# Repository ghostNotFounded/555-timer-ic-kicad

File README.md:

# 555 Timer IC Project using KiCad

## Overview
This repository contains the schematic and PCB design files for a 555 Timer IC circuit created using KiCad. The project was undertaken as part of the learning process for KiCad and to contribute to joining the robotics team at CRiSS Robotics on campus.

## Contents
- **Schematic**: Contains the schematic design of the 555 Timer IC circuit.
- **PCB Layout**: Includes the PCB layout design based on the schematic.

## Purpose
The purpose of this project was to:
- Learn KiCad, a popular open-source EDA tool for circuit design and PCB layout.
- Gain hands-on experience in designing a simple circuit using a widely-used IC, the 555 Timer.
- Prepare to contribute to the robotics team at CRiSS Robotics, showcasing skills in circuit design and layout.

## How to Use
1. Clone or download the repository to your local machine.
2. Open the schematic and PCB layout files using KiCad.
3. Review the designs, make any necessary modifications, and generate Gerber files for manufacturing if required.

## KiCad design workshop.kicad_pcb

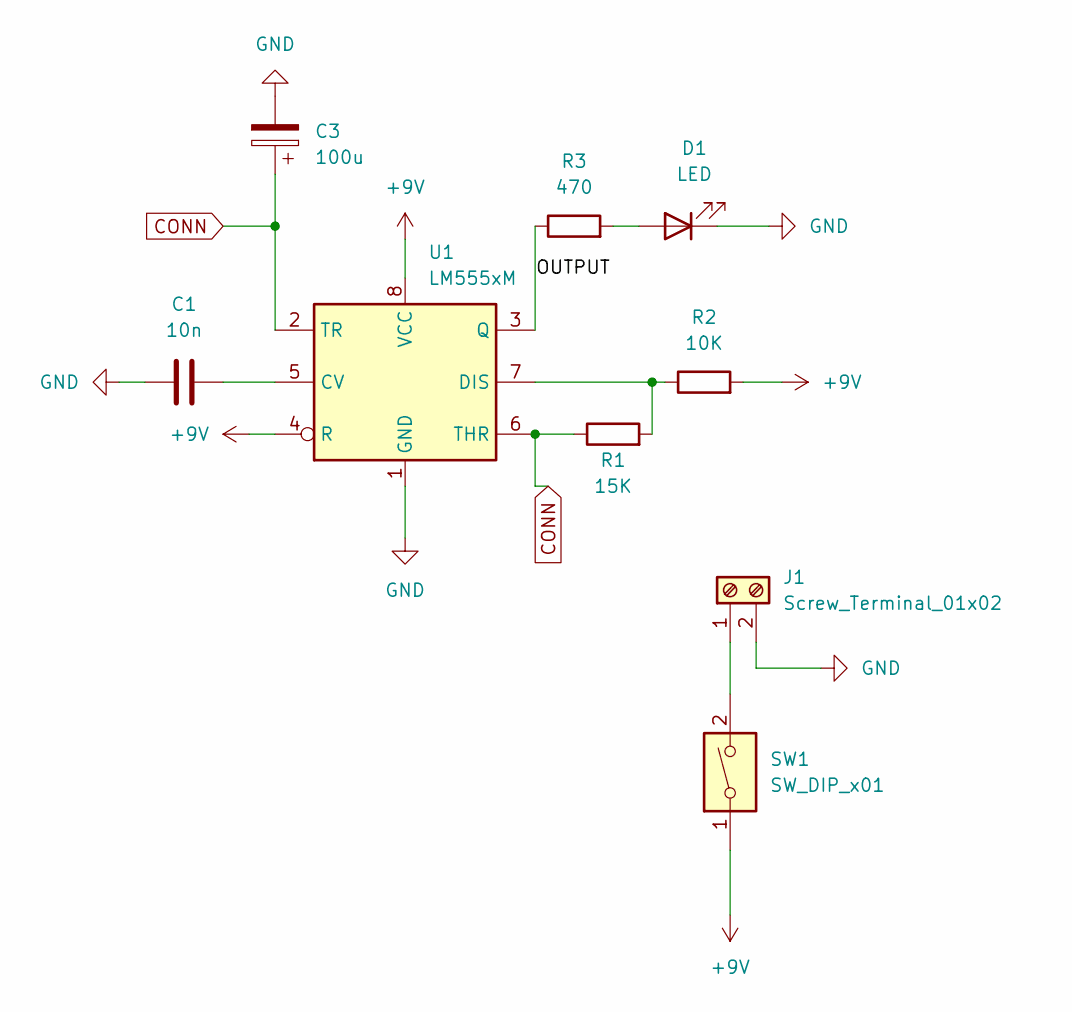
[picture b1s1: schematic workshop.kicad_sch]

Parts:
C1: 10n; C_Disc_D4.7mm_W2.5mm_P5.00mm
C3: 100u; CP_Radial_D12.5mm_P7.50mm
D1: LED; LED_D5.0mm
J1: Screw_Terminal_01x02; BarrelJack_CUI_PJ-063AH_Horizontal
R1: 15K; R_Axial_DIN0207_L6.3mm_D2.5mm_P10.16mm_Horizontal
R2: 10K; R_Axial_DIN0207_L6.3mm_D2.5mm_P10.16mm_Horizontal
R3: 470; R_Axial_DIN0207_L6.3mm_D2.5mm_P10.16mm_Horizontal
SW1: SW_DIP_x01; SW_DIP_SPSTx01_Slide_6.7x4.1mm_W7.62mm_P2.54mm_LowProfile
U1: LM555xM; SOIC-8_3.9x4.9mm_P1.27mm

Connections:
+9V: R2.2, SW1.1, U1.4 (R), U1.8 (VCC)
/OUTPUT: R3.1, U1.3 (Q)
CONN: C3.1, R1.1, U1.2 (TR), U1.6 (THR)
GND: C1.1, C3.2, D1.1 (K), J1.2, U1.1 (GND)
unnamed: D1.2 (A), R3.2
unnamed: J1.1, SW1.2
unnamed: C1.2, U1.5 (CV)
unnamed: R1.2, R2.1, U1.7 (DIS)

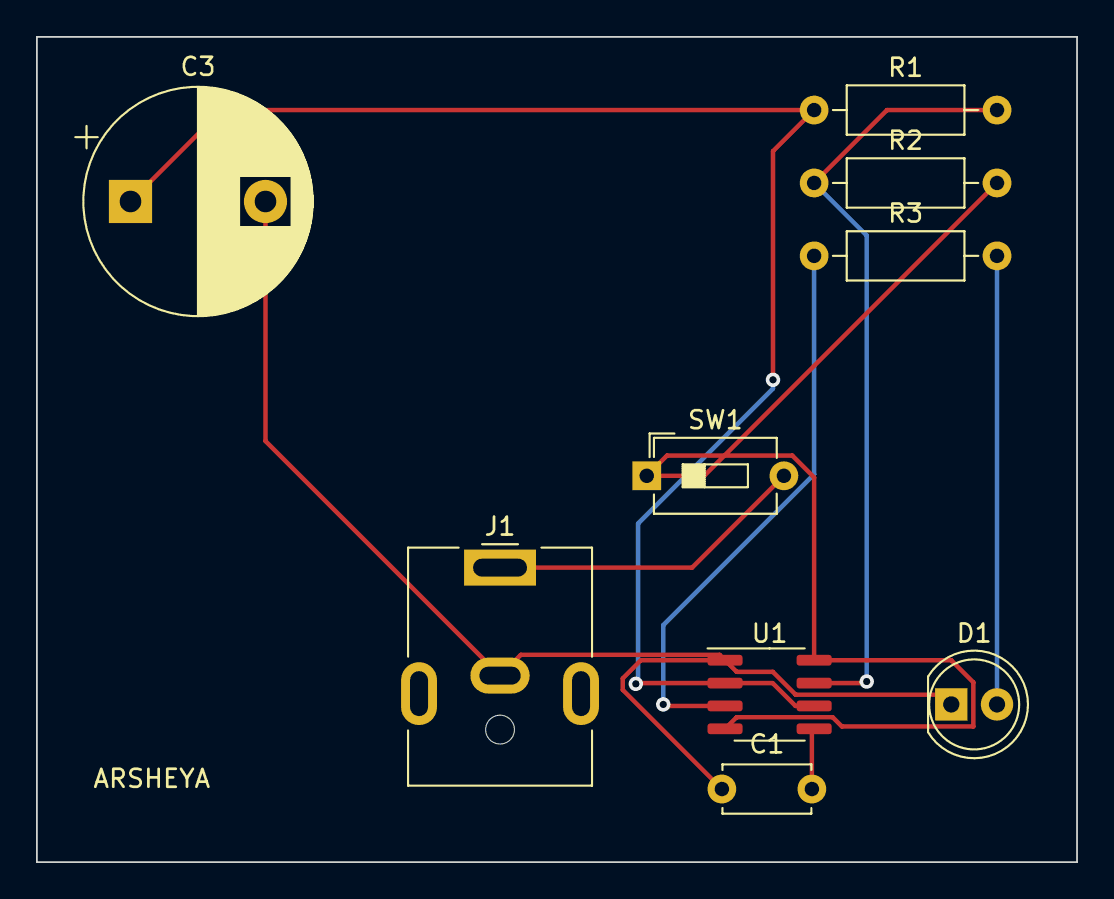
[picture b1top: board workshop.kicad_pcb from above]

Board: 2 copper layers, 57.8 x 45.8 mm, 9 parts (0 on the bottom side), 8 nets.

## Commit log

2024-02-28 completed files
